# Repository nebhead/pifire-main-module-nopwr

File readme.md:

# PiFire Main Module PCB (v4.x.x) KiCad Files

## What is this? 

This PCB provides a modular approach to building your PiFire Smart Smoker Controller.  This board breaks out the many interfaces that are commonly used to support sensors, relays, displays and other devices.  This design allows the user to choose features that suit their needs such as using a PWM DC Fan instead of the AC fan system, or allows for different and expanded probe devices.  Some other notable features are the addition of a 1-Wire bus connector, a wake/shutdown option, and more!  

__Important Notes:__  
1. This board requires v1.8.x of PiFire or later.  As of May 2024, this version is still in development and can be tested by switching to the development branch in the updater page.  Ensure you run through the configuration wizard to select the v4.x.x board and configure your specific settings appropriately. 
1. This board does NOT support the selector switch to run in parallel with the OEM controller.  The pin used for this purpose has been repurposed for the wake/shutdown feature. 

The design intent for this board was to make a DIY accessible PCB that can be more easily put together by the maker/enthusiast of almost any skill level.  Full size components are used in most cases and most (if not all) parts should be readily available to order online.  See the [Interactive BOM](#interactive-bom) for more details about the parts used and links to order.

### What is PiFire? 

PiFire is a SBC based Pellet Smoker Controller.  More details can be found [here](https://nebhead.github.io/PiFire) or [at the GitHub repo](https://github.com/nebhead/pifire). 

## What's in this Repository?

### KiCad Project Files 
In this repository you will find the latest KiCad design files for the  PCB.  Simply load the project file (.kicad_pro) into the KiCad software and you should be able to edit as needed.  Or if you just want to get this board made, jump to the production section below.

### Interactive BOM

There is an interactive BOM located in the [/bom](bom/) folder which details the parts and provides some pin information as well.  Use this to gather the components you may need to build this board out and refer back to it for placement help.    

[BOM + Pin Info](https://nebhead.github.io/pifire-main-module-nopwr)

_This is a standalone HTML file that was autogenerated by the excellent plugin for KiCad. See the plugin here: [https://github.com/openscopeproject/InteractiveHtmlBom](https://github.com/openscopeproject/InteractiveHtmlBom)_

### PDF of the Schematic

Preview the schematic in PDF format here: [Schematic](schematic.pdf)

### JLCPCB Production Files

If you wish to get these PCBs made by JLCPCB, the production files are provided in the `/production` folder.  For convenience, the file `production.zip` can simply be uploaded to JLCPCB to make it super easy to order boards.

Drop the zip file onto the order page, wait for it to upload then simply continue to order the board.  Optionally, select different board color, PCB quantity, surface finish, etc.  Most of the default settings should be sufficient. 

### Links to the PCBs in this family of PiFire Boards

This PCB is part of a family of PCBs that can be used together to create  a full PiFire system.  Generally speaking you need the Main Module/Board, a Relay Control Board and a Probe Device board to have a basic PiFire system.  

**Main Module/Board** (required)
* [Main Board v4.0.x](https://github.com/nebhead/pifire-main-module-nopwr)

**Relay/Fan Control Boards** (choose one)
* [Mechanical Relay Module](https://github.com/nebhead/pifire-relay-module)
* [Solid State Relay Module](https://github.com/nebhead/pifire-relay-module-SSR)
* [Solid State Relay + PWM Fan Module](https://github.com/nebhead/pifire-relay-pwm-module-ssr) - Original Design
* [Solid State Relay + PWM Fan Module Alternate](https://github.com/nebhead/pifire-relay-pwm-module-ssr-alt) - Updated Design (Designed with help from @labmonkeyrat on Discord)

**Probe Device Board** (optional)
* [ADS Board](https://github.com/nebhead/pifire-ads-board) 

### General 4.x.x PCB Architecture

Sometimes it is easier to understand how a project is built out by looking at the general architecture.  I've created a high-level diagram of the project so that you can get an idea of how all of this should be connected up. 

The first diagram is of the AC Fan Version of the system.  This version only requires a 5V power supply and only uses a portion of the headers to connect to a relay board.  Technically speaking, in this configuration you could use an off the shelf relay board if you wanted to wire this up yourself.

The second diagram is of the DC PWM Fan version of the system.  You'll notice that this version utilizes a 5V/12V power-supply and the specially design relay/PWM Fan board.  

### PCB 4.x.x Pinout

Due to space constraints on the PCB silkscreen layer, most of the pins for the JST connectors are unmarked.  Thus I'm providing a handy set of images for the pinout of the major unmarked JST connectors. 

___Buttons & Encoder Header___

___1-Wire Header___ - _Used for the DS18B20 reference probe.  Great for using as a reference to tune your other probes._

___Relay and PWM Fan Headers___ - _If you are not using the DC Fan, then only the top header needs to be populated._

___Auxiliary SPI Header___ - _If you are already using the display SPI header, this can be used for another SPI based device such as the MAX38165 RTD probe device._

```note
You must bridge solder jumpers on the back the board to select Chip Enable 0, Chip Enable 1 or GPIO6 (CE0/CE1/GPIO6) and 3.3V or 5V.  Do not bridge both 3.3V and 5V or CE0 and CE1 at the same time or you may damage your system.
```

___Display SPI Header___ - _If you are using a SPI based display like the ILI9341, then this header should match the pinout for that display._

```note
You must bridge solder jumpers on the back the board to select Chip Enable 0 or 1 (CE0/CE1) and 3.3V or 5V.  Do not bridge both 3.3V and 5V or CE0 and CE1 at the same time or you may damage your system.
```

___I2C Headers___ - _All of the I2C headers pinouts are identical and can be used for any of the I2C devices including the ADC board, an I2C display, or an I2C distance device._

### 3D Printable Enclosures/Boxes 

With all of the 3D Prints for PiFire, a higher temperature filament such as PETG should be used.  PLA generally won't stand up to the temperatures that the components may be exposed to outdoors and near a hot smoker.  

#### Pi Zero W/2W Enclosure

An initial revision of the enclosure for this, supporting the Raspberry Pi Zero W/2W (and may actually also support the Raspberry Pi 3A+ but has not been tested).  The current models should be considered still in development and may have alignment challenges, etc. 

Except for the mounting wings and the Raspberry Pi mounts, the majority of bolts to be used with this enclosure are M3. 

* STL: [Base](/printables/PiFire-v4-PiZero-Base.stl)
* STL: [Lid](/printables/PiFire-v4-PiZero-Lid.stl)
* OnShape: [Enclosure Original Models](https://cad.onshape.com/documents/3596921e7143afe3464ba577/w/28c0bdfc90c946dc2a56d7d1/e/2ad9de1bc228faf5a8cd0384?renderMode=0&uiState=66e0db844db84570fca6f1d5)

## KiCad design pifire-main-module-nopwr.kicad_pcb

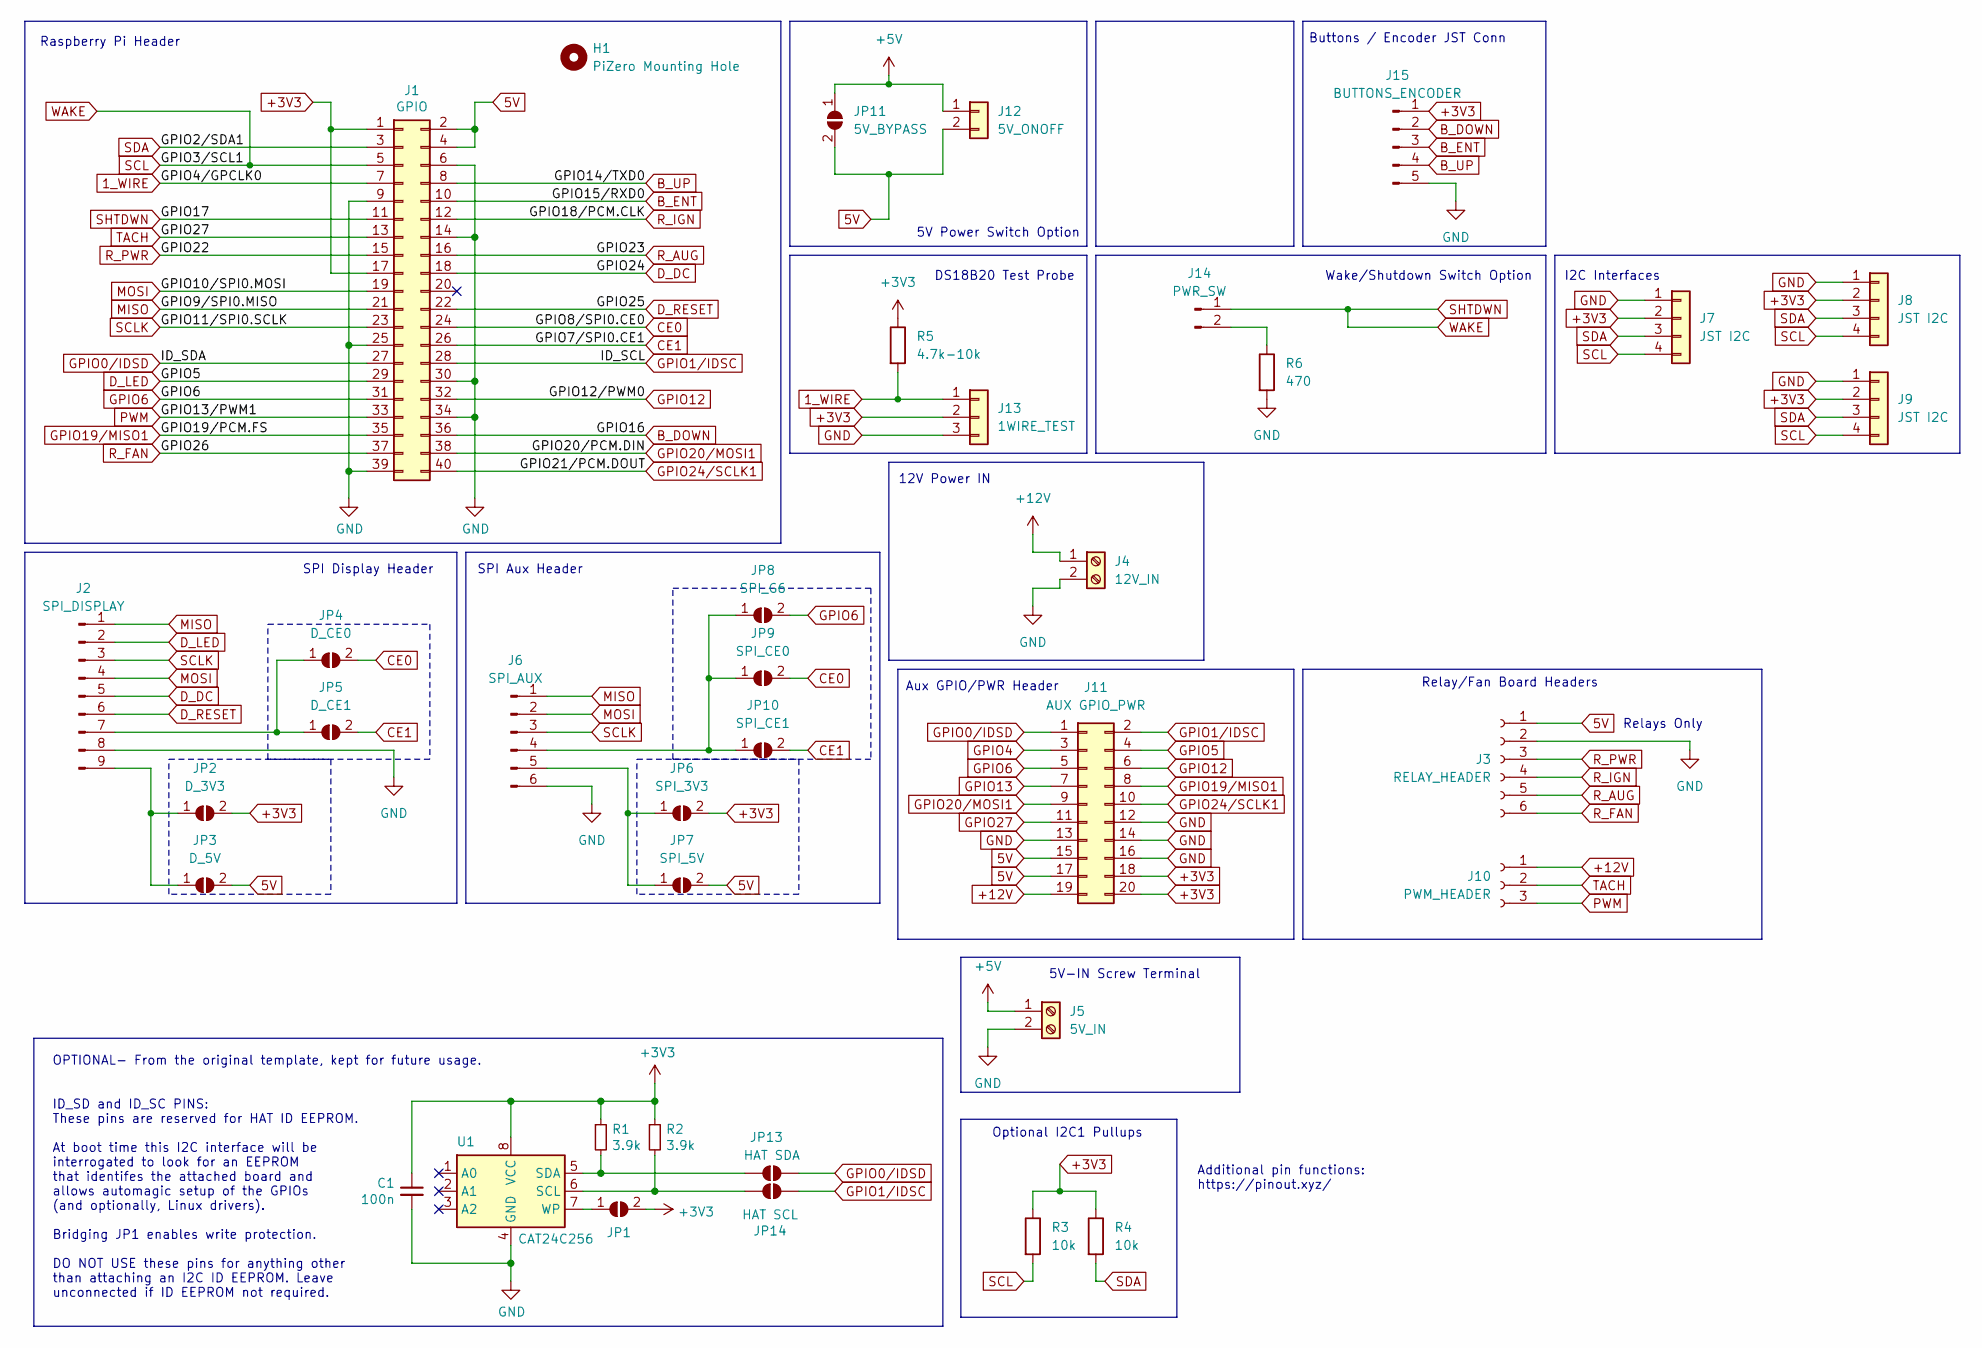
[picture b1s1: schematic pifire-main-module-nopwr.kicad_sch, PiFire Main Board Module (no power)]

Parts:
C1: 100n; C_Disc_D3.0mm_W1.6mm_P2.50mm
H1: PiZero Mounting Hole; MountingHole_2.7mm_M2.5
J1: GPIO; PinSocket_2x20_P2.54mm_Vertical
J2: SPI_DISPLAY; JST_XH_B9B-XH-A_1x09_P2.50mm_Vertical
J3: RELAY_HEADER; JST_XH_B6B-XH-A_1x06_P2.50mm_Vertical
J4: 12V_IN; TerminalBlock_bornier-2_P5.08mm
J5: 5V_IN; TerminalBlock_bornier-2_P5.08mm
J6: SPI_AUX; JST_XH_B6B-XH-A_1x06_P2.50mm_Vertical
J7, J8, J9: JST I2C; JST_XH_B4B-XH-A_1x04_P2.50mm_Vertical
J10: PWM_HEADER; JST_XH_B3B-XH-A_1x03_P2.50mm_Vertical
J11: AUX GPIO_PWR; PinSocket_2x10_P2.54mm_Vertical
J12: 5V_ONOFF; JST_XH_B2B-XH-A_1x02_P2.50mm_Vertical
J13: 1WIRE_TEST; JST_XH_B3B-XH-A_1x03_P2.50mm_Vertical
J14: PWR_SW; JST_XH_B2B-XH-A_1x02_P2.50mm_Vertical
J15: BUTTONS_ENCODER; JST_XH_B5B-XH-A_1x05_P2.50mm_Vertical
JP1: ID_WP; SolderJumper-2_P1.3mm_Open_TrianglePad1.0x1.5mm
JP2: D_3V3; SolderJumper-2_P1.3mm_Open_TrianglePad1.0x1.5mm
JP3: D_5V; SolderJumper-2_P1.3mm_Open_TrianglePad1.0x1.5mm
JP4: D_CE0; SolderJumper-2_P1.3mm_Open_TrianglePad1.0x1.5mm
JP5: D_CE1; SolderJumper-2_P1.3mm_Open_TrianglePad1.0x1.5mm
JP6: SPI_3V3; SolderJumper-2_P1.3mm_Open_TrianglePad1.0x1.5mm
JP7: SPI_5V; SolderJumper-2_P1.3mm_Open_TrianglePad1.0x1.5mm
JP8: SPI_G6; SolderJumper-2_P1.3mm_Open_TrianglePad1.0x1.5mm
JP9: SPI_CE0; SolderJumper-2_P1.3mm_Open_TrianglePad1.0x1.5mm
JP10: SPI_CE1; SolderJumper-2_P1.3mm_Open_TrianglePad1.0x1.5mm
JP11: 5V_BYPASS; SolderJumper-2_P1.3mm_Open_TrianglePad1.0x1.5mm
JP13: HAT SDA; SolderJumper-2_P1.3mm_Open_TrianglePad1.0x1.5mm
JP14: HAT SCL; SolderJumper-2_P1.3mm_Open_TrianglePad1.0x1.5mm
R1, R2: 3.9k; R_Axial_DIN0207_L6.3mm_D2.5mm_P7.62mm_Horizontal
R3, R4: 10k; R_Axial_DIN0207_L6.3mm_D2.5mm_P7.62mm_Horizontal
R5: 4.7k-10k; R_Axial_DIN0207_L6.3mm_D2.5mm_P7.62mm_Horizontal
R6: 470; R_Axial_DIN0207_L6.3mm_D2.5mm_P7.62mm_Horizontal
U1: CAT24C256; SOIC-8_3.9x4.9mm_P1.27mm

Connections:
1_WIRE: J1.7, J13.1, R5.2
5V: J1.2, J1.4, J3.1, J11.15, J11.17, J12.2, JP3.2 (B), JP7.2 (B), JP11.2 (B)
+3V3: C1.1, J1.1, J1.17, J7.2, J8.2, J9.2, J11.18, J11.20, J13.2, J15.1, JP1.2 (B), JP2.2 (B), JP6.2 (B), R1.1, R2.1, R3.1, R4.1, R5.1, U1.8 (VCC)
+5V: J5.1, J12.1, JP11.1 (A)
+12V: J4.1, J10.1, J11.19
B_DOWN: J1.36, J15.2
B_ENT: J1.10, J15.3
B_UP: J1.8, J15.4
CE0: J1.24, JP4.2 (B), JP9.2 (B)
CE1: J1.26, JP5.2 (B), JP10.2 (B)
D_DC: J1.18, J2.5
D_LED: J1.29, J2.2, J11.4
D_RESET: J1.22, J2.6
GND: C1.2, J1.6, J1.9, J1.14, J1.25, J1.30, J1.34, J1.39, J2.8, J3.2, J4.2, J5.2, J6.6, J7.1, J8.1, J9.1, J11.12, J11.13, J11.14, J11.16, J13.3, J15.5, R6.2, U1.4 (GND)
GPIO0/IDSD: J1.27, J11.1, JP13.2 (B)
GPIO1/IDSC: J1.28, J11.2, JP14.2 (B)
GPIO4: J11.3
GPIO6: J1.31, J11.5, JP8.2 (B)
GPIO12: J1.32, J11.6
GPIO13: J11.7
GPIO19/MISO1: J1.35, J11.8
GPIO20/MOSI1: J1.38, J11.9
GPIO24/SCLK1: J1.40, J11.10
GPIO27: J1.13, J10.2, J11.11
MISO: J1.21, J2.1, J6.1
MOSI: J1.19, J2.4, J6.2
unnamed: J2.7, JP4.1 (A), JP5.1 (A)
unnamed: J2.9, JP2.1 (A), JP3.1 (A)
unnamed: J6.4, JP8.1 (A), JP9.1 (A), JP10.1 (A)
unnamed: J6.5, JP6.1 (A), JP7.1 (A)
unnamed: J14.2, R6.1
unnamed: JP1.1 (A), U1.7 (WP)
unnamed: JP13.1 (A), R1.2, U1.5 (SDA)
unnamed: JP14.1 (A), R2.2, U1.6 (SCL)
PWM: J1.33, J10.3
R_AUG: J1.16, J3.5
R_FAN: J1.37, J3.6
R_IGN: J1.12, J3.4
R_PWR: J1.15, J3.3
SCL: J1.5, J1.11, J7.4, J8.4, J9.4, J14.1, R3.2
SCLK: J1.23, J2.3, J6.3
SDA: J1.3, J7.3, J8.3, J9.3, R4.2

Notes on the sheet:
Relays Only
SPI Display Header
Raspberry Pi Header
Relay/Fan Board Headers
Buttons / Encoder JST Conn
Additional pin functions: https://pinout.xyz/
DS18B20 Test Probe
Aux GPIO/PWR Header
Optional I2C1 Pullups
12V Power IN
I2C Interfaces
ID_SD and ID_SC PINS: These pins are reserved for HAT ID EEPROM. At boot time this I2C interface will be interrogated to look for an EEPROM that identifes the attached board and allows automagic setup of the GPIOs (and optionally, Linux drivers). Bridging JP1 enables write protection. DO NOT USE th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
OPTIONAL- From the original template, kept for future usage.
SPI Aux Header
5V-IN Screw Terminal
5V Power Switch Option
Wake/Shutdown Switch Option

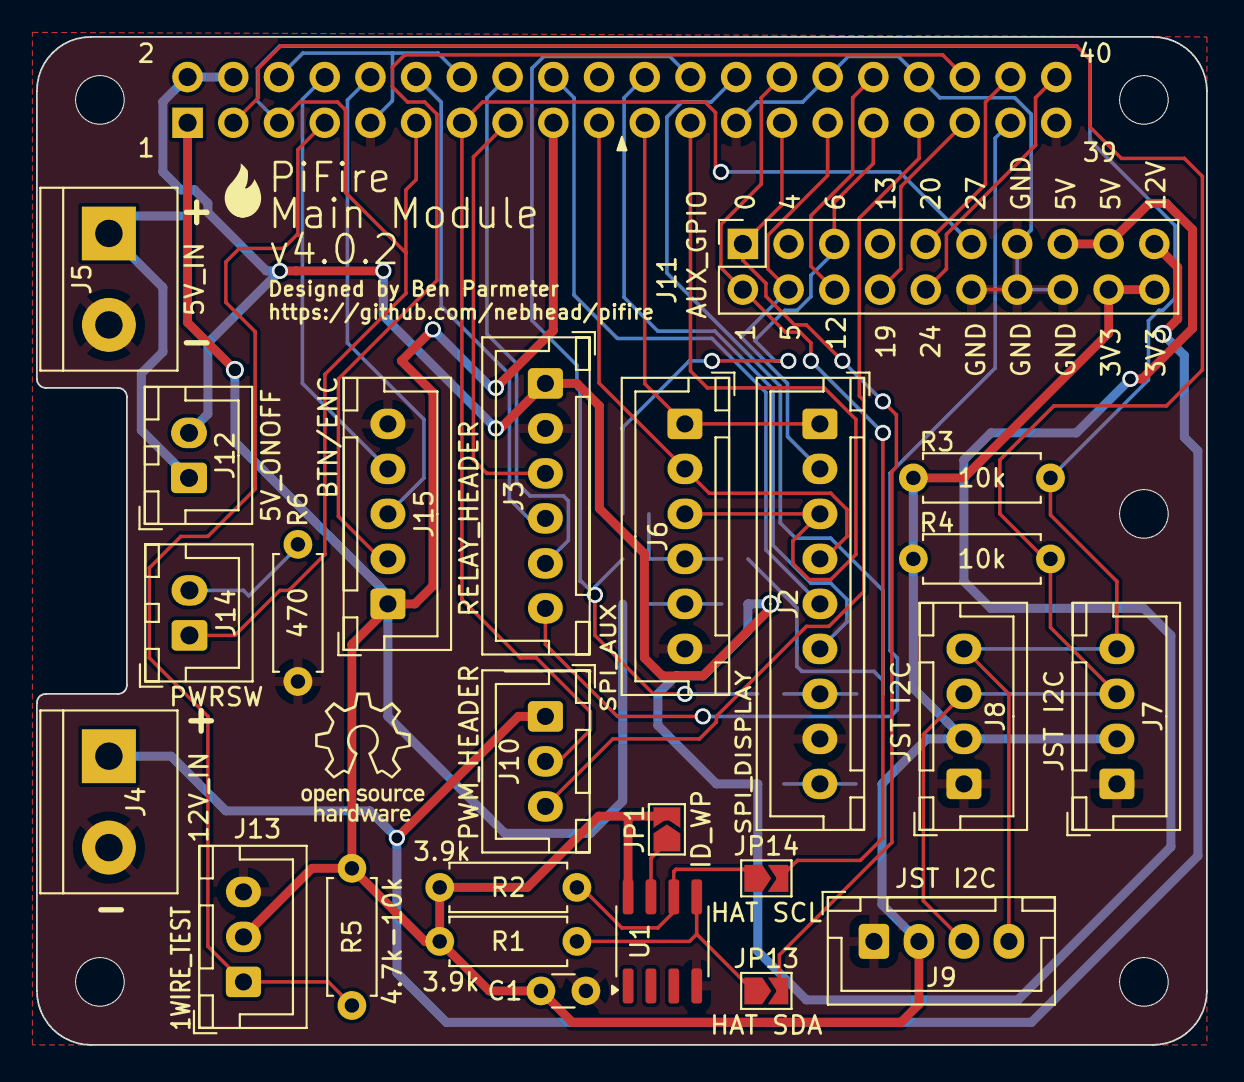
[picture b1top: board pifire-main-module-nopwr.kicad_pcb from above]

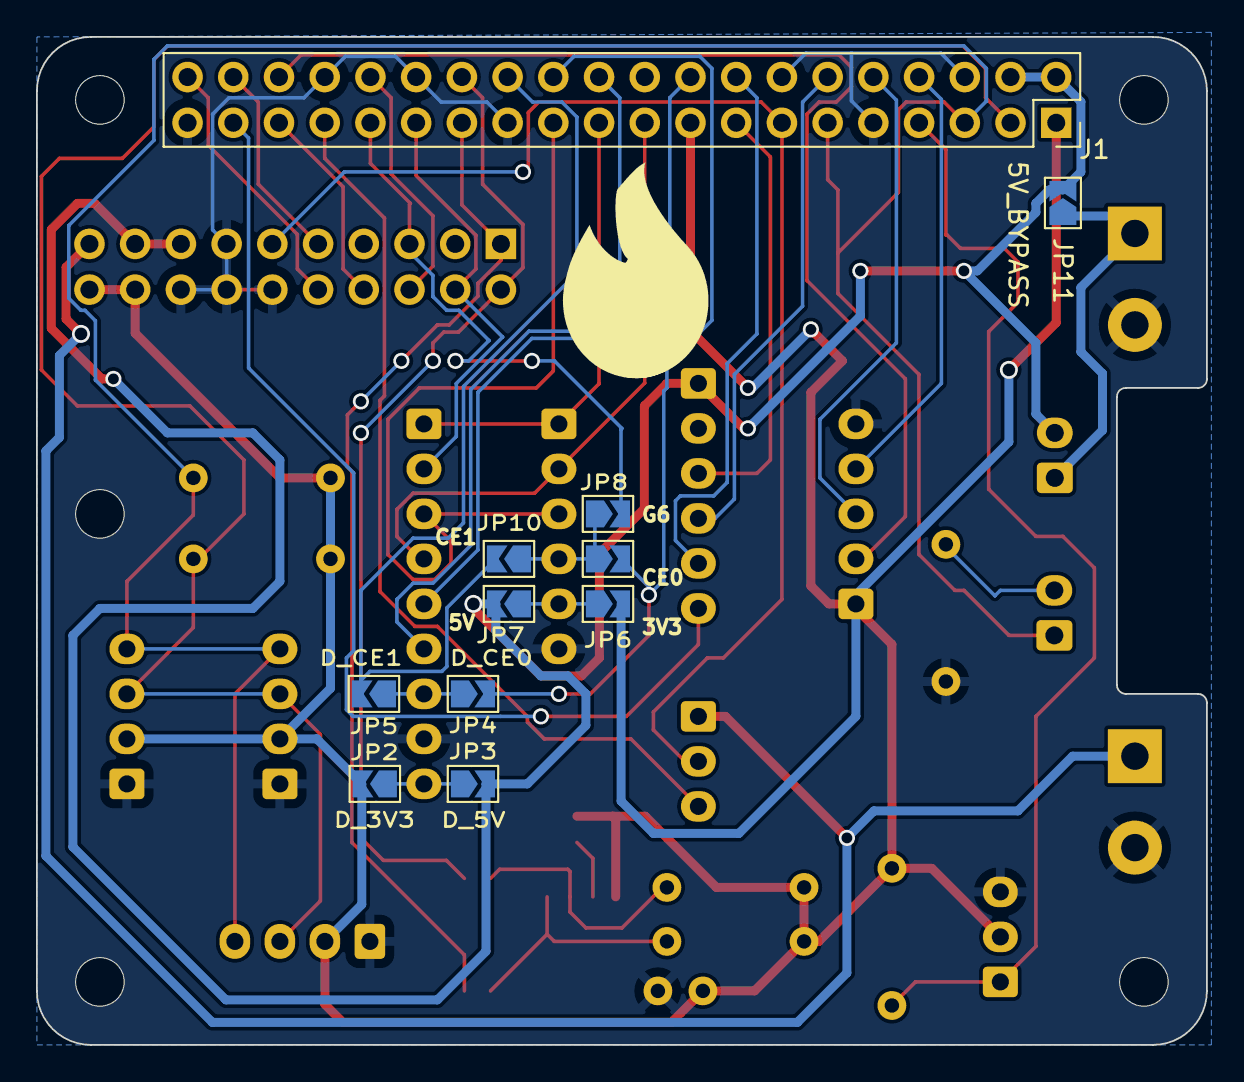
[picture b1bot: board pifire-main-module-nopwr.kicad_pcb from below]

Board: 2 copper layers, 65.0 x 56.0 mm, 41 parts (11 on the bottom side), 40 nets.

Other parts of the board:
MH1, MH2, MH3, MH4: MountingHole_2.7mm_M2.5

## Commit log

2024-05-07 Updated to v4.0.2
    Split PWM pins out of the Relay/Fan header to create two headers. This makes the board design more modular going forward and makes it easier to source the smaller 6 pin JST header.
2024-05-10 Updated Documentation
2024-09-07 Update readme.md
    Updating PWM links.
2024-09-11 Added Pinout, High Level Schematic, and 3D Printables
    Added pinout pictures to help with building out cables for external components.
    Added high level schematic to explain where this board fits in the system.
    Added 3D printable files/links for Pi Zero W/2W.
2025-04-08 Updated with I2C pinout image
